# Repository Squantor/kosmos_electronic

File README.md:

# Kosmos electronic bits and pieces
This repository contains various bits and pieces that can be used with the Kosmos electronic series experiment kits. 
## Structure
* [Electronics](electronics/README.md) contains the schematics and PCB's used by the project

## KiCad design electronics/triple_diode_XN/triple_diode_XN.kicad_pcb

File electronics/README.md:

# Kosmos electronic modules
This directory contains mostly reproductions or new modules for the Kosmos electronics experiment kits. The schematics and PCB's are drawn in kicad. Most of the modules are described in "unit cells". The transistor modules are one unit cell large. The MW/AM module and opamp module are two unit cells large. The 555 module from the XN3000 box is a 3 cell large module.

There exist also "double density" modules used in the XN3000 series box. Here the unitcell is subdivided, this to acommodate components with high pin counts like the LM324 quad opamp or some 4000 series logic. I might need to modify some XN boards to measure the size of these modules so I might prototype them.

The [Kosmos electronic radio tech](https://www.youtube.com/watch?v=OwKrZVnxMPc) has a few very interesting modules. I would love to get my hands on those and try some experiments with them and recreate the modules. It contains 

But why not create your own modules? I have a few ideas, useful for all kinds of experiments and prototyping. Feel free to add an issue for module ideas to add them to the planned modules.
# Created modules
* [one by one cell template](template_1by1/README.md)
* [one by two cell template](template_1by2/README.md)
* [one by three cell template](template_1by3/README.md)
* [two by two cell template](template_2by2/README.md)
* [one by one cell prototyping board](proto_1by1/README.md)
* [one by two cell prototyping board](proto_1by2/README.md)
* [two by two cell prototyping board](proto_2by2/README.md)
* [NPN transistor Through Hole](NPN_transistor_TH/README.md)
* [PNP transistor Through Hole](PNP_transistor_TH/README.md)
* [NMOS transistor Through Hole](NMOS_transistor_TH/README.md)
* [PMOS transistor Through Hole](PMOS_transistor_TH/README.md)
* [Generic transistor SOT23](transistor_SOT23/README.md)
# Planned modules
* Prototyping boards for all the templates, useful for adding your own circuits
* TL431 adjustable zener
* NE555 just like in the XN3000 box
* General purpose dual opamp board, fit with a socket so any dual opamp can be fitted
* LM321 single opamp
* Audio Amp module as used in the X2000 and XN2000 based on the [TBA820M](https://lcsc.com/product-detail/Audio-Power-OpAmps_UTC-Unisonic-Tech-TBA820ML-D08-T_C171467.html)
* Single optocoupler
* Dual photodiode optocoupler, useful for analog isolator experiments?
* SA612 gilbert cell mixer, this module was used in the Kosmos electronic radio tech but has an unusual size, seems like a 2 by 2 unit cell module but fitting a higher density top?
* SA612 gilbert cell mixer but in a three by one format, more useful for all kinds of experiments
* Crystal/filter on a single cell module, the filter was present in the radio tech box
* SA612 mixer based down converter, to make a X1000/XN1000 short wave radio or a direct conversion receiver.
# TODO's

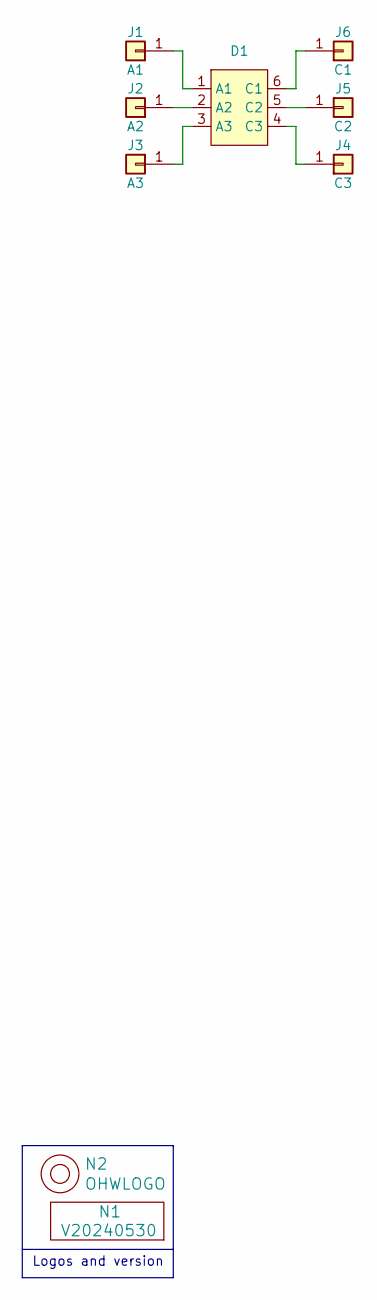
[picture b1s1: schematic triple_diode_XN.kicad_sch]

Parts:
D1: SOT363-NXP-hand
J1: A1; PC_pin_nail_head_6092
J2: A2; PC_pin_nail_head_6092
J3: A3; PC_pin_nail_head_6092
J4: C3; PC_pin_nail_head_6092
J5: C2; PC_pin_nail_head_6092
J6: C1; PC_pin_nail_head_6092
N1: V20240530; Label_Generic
N2: OHWLOGO; OSHW-Symbol_6.7x6mm_SilkScreen

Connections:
unnamed: D1.1 (A1), J1.1
unnamed: D1.2 (A2), J2.1
unnamed: D1.3 (A3), J3.1
unnamed: D1.6 (C1), J6.1
unnamed: D1.5 (C2), J5.1
unnamed: D1.4 (C3), J4.1

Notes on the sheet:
Logos and version

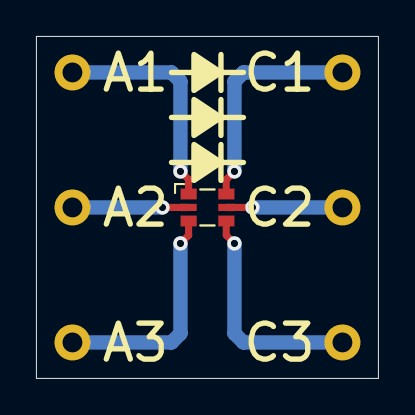
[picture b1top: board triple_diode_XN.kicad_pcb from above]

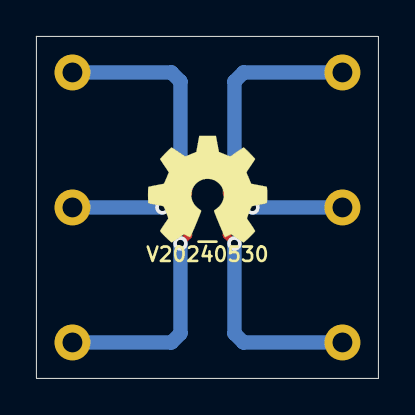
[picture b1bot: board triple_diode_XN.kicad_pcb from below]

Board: 2 copper layers, 19.0 x 19.0 mm, 9 parts (2 on the bottom side), 6 nets.

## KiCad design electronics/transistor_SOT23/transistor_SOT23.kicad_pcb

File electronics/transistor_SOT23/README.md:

# Kosmos electronic SOT23 transistor
Kosmos electronic generic SOT23 transistor, as far as I know most SOT23 transistors, BJT or MOSFET, all have the same pinout.
1. Base or Gate
2. Emitter or Source
3. Collector or Drain
## TODO's
Still some things need to be done:
* Manufacturing
* Test
* Pictures
## BOM
* Kosmos electronic uses some special pins for the connections, I have found something similar by [Mill-max 6092](https://www.mill-max.com/catalog/download/2020-10%3A207M.pdf) available at [digikey](https://www.digikey.com/en/products/detail/mill-max-manufacturing-corp/6092-0-00-15-00-00-33-0/1991698)
* BC547 style PNP transistor

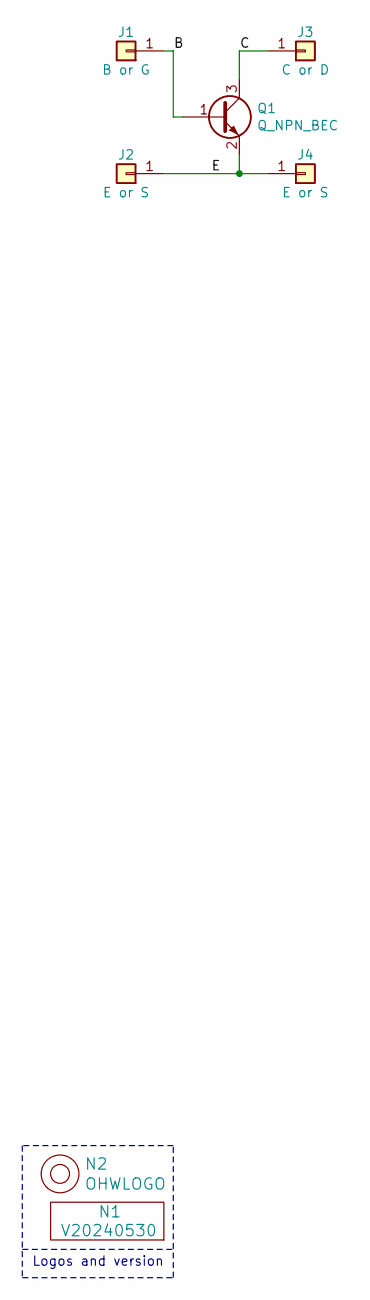
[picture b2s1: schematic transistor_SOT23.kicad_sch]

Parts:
J1: B or G; PC_pin_nail_head_6092
J2, J4: E or S; PC_pin_nail_head_6092
J3: C or D; PC_pin_nail_head_6092
N1: V20240530; Label_Generic
N2: OHWLOGO; OSHW-Symbol_6.7x6mm_SilkScreen
Q1: Q_NPN_BEC; SOT23-3

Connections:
/B: J1.1, Q1.1 (B)
/C: J3.1, Q1.3 (C)
/E: J2.1, J4.1, Q1.2 (E)

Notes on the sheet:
Logos and version

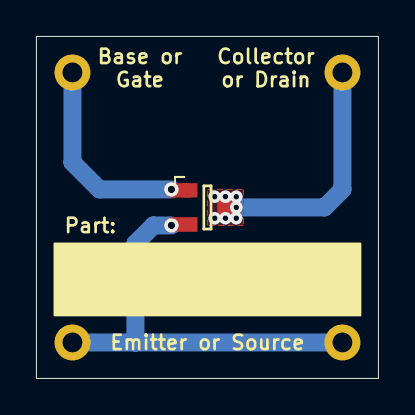
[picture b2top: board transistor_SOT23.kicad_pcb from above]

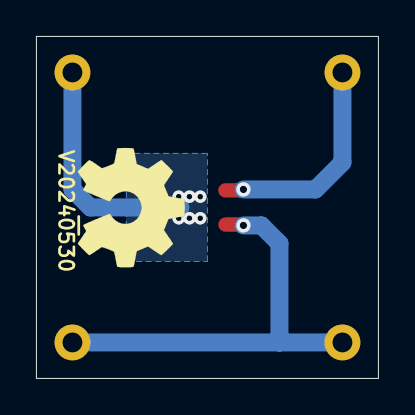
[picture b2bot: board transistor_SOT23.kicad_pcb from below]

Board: 2 copper layers, 19.0 x 19.0 mm, 7 parts (2 on the bottom side), 3 nets.

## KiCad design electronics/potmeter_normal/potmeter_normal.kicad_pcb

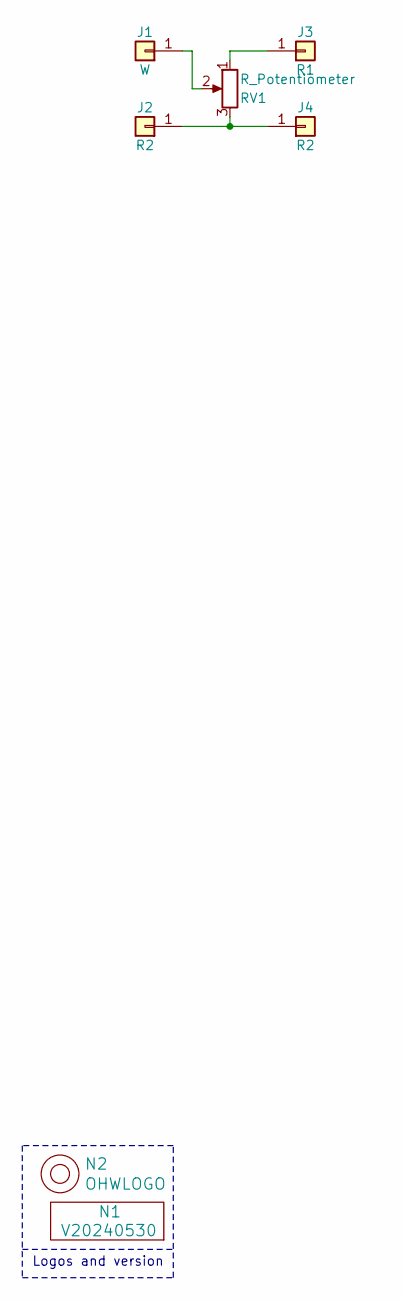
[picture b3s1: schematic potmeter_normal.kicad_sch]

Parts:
J1: W; PC_pin_nail_head_6092
J2, J4: R2; PC_pin_nail_head_6092
J3: R1; PC_pin_nail_head_6092
N1: V20240530; Label_Generic
N2: OHWLOGO; OSHW-Symbol_6.7x6mm_SilkScreen
RV1: R_Potentiometer; Potentiometer_Piher_PT-15-V15_Vertical

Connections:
unnamed: J1.1, RV1.2
unnamed: J2.1, J4.1, RV1.3
unnamed: J3.1, RV1.1

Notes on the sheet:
Logos and version

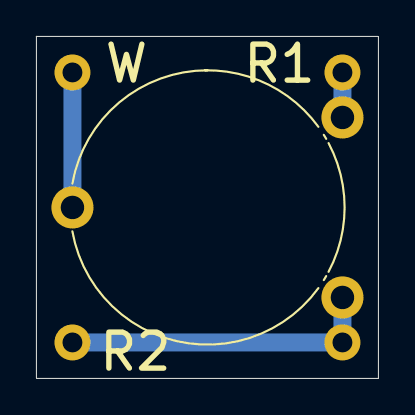
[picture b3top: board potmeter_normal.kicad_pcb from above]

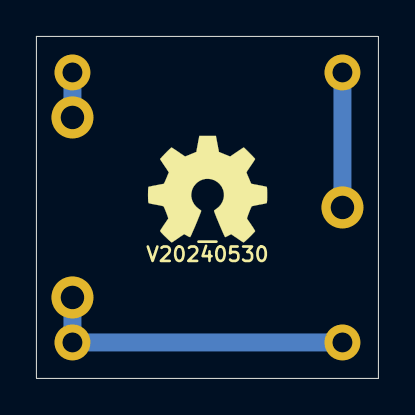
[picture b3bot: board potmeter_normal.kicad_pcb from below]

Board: 2 copper layers, 19.0 x 19.0 mm, 7 parts (2 on the bottom side), 3 nets.

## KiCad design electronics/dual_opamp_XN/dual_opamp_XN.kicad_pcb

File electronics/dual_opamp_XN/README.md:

# One by Two module template high density for Kosmos Elektronic XN
Template for a one by two sized module for the Kosmos XN1000 series experiment boxes.
## BOM
* The X1000 and XN1000 special pins for the connections, I have found something similar by [Mill-max 6092](https://www.mill-max.com/catalog/download/2020-10%3A207M.pdf) available at [digikey](https://www.digikey.com/en/products/detail/mill-max-manufacturing-corp/6092-0-00-15-00-00-33-0/1991698)

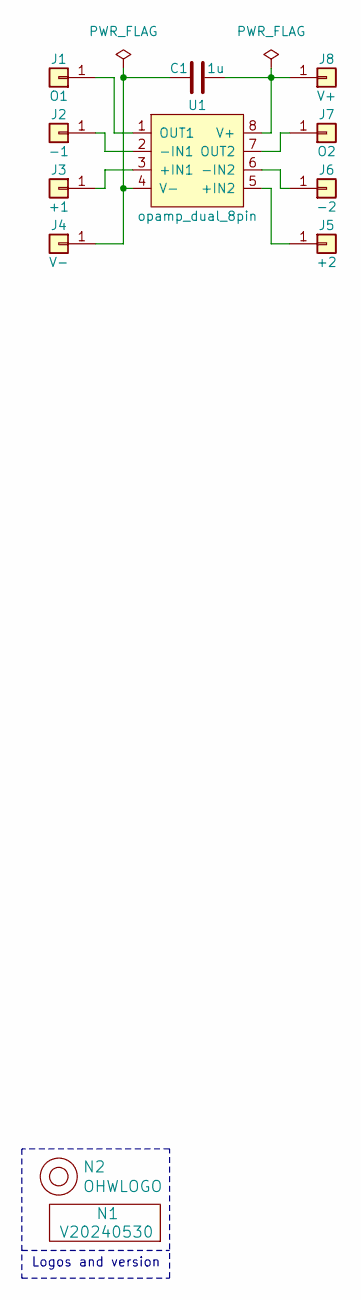
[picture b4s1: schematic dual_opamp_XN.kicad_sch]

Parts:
C1: 1u; C-050-050X100-0805-3516-film
J1: O1; PC_pin_nail_head_6092
J2: -1; PC_pin_nail_head_6092
J3: +1; PC_pin_nail_head_6092
J4: V-; PC_pin_nail_head_6092
J5: +2; PC_pin_nail_head_6092
J6: -2; PC_pin_nail_head_6092
J7: O2; PC_pin_nail_head_6092
J8: V+; PC_pin_nail_head_6092
N1: V20240530; Label_Generic
N2: OHWLOGO; OSHW-Symbol_6.7x6mm_SilkScreen
U1: opamp_dual_8pin; DIP-8_W7.62mm_Socket

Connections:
unnamed: J1.1, U1.1 (OUT1)
unnamed: J2.1, U1.2 (-IN1)
unnamed: J3.1, U1.3 (+IN1)
unnamed: C1.1, J4.1, U1.4 (V-)
unnamed: J5.1, U1.5 (+IN2)
unnamed: J6.1, U1.6 (-IN2)
unnamed: J7.1, U1.7 (OUT2)
unnamed: C1.2, J8.1, U1.8 (V+)

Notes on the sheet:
Logos and version

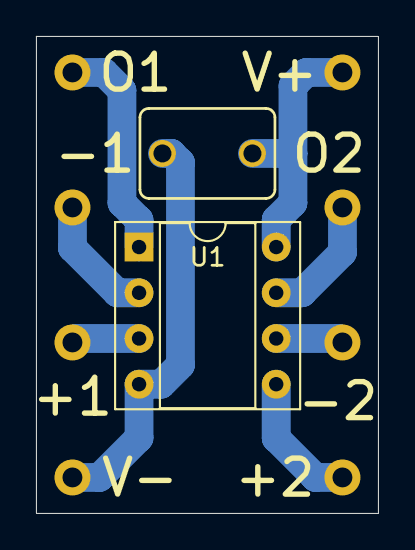
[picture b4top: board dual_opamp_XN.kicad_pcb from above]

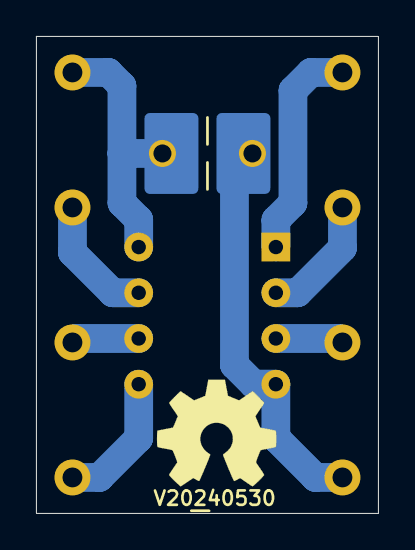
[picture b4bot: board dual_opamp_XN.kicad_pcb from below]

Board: 2 copper layers, 19.0 x 26.5 mm, 12 parts (2 on the bottom side), 8 nets.

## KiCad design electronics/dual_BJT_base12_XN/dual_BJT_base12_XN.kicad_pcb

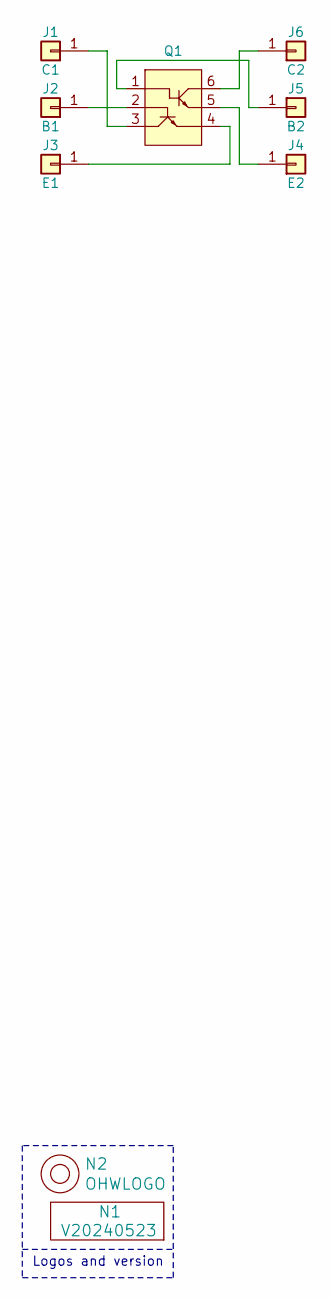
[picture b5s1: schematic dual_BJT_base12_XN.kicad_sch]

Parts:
J1: C1; PC_pin_nail_head_6092
J2: B1; PC_pin_nail_head_6092
J3: E1; PC_pin_nail_head_6092
J4: E2; PC_pin_nail_head_6092
J5: B2; PC_pin_nail_head_6092
J6: C2; PC_pin_nail_head_6092
N1: V20240523; Label_Generic
N2: OHWLOGO; OSHW-Symbol_6.7x6mm_SilkScreen
Q1: SOT363-NXP-hand

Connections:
unnamed: J1.1, Q1.3
unnamed: J2.1, Q1.2
unnamed: J3.1, Q1.4
unnamed: J4.1, Q1.5
unnamed: J5.1, Q1.1
unnamed: J6.1, Q1.6

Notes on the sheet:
Logos and version

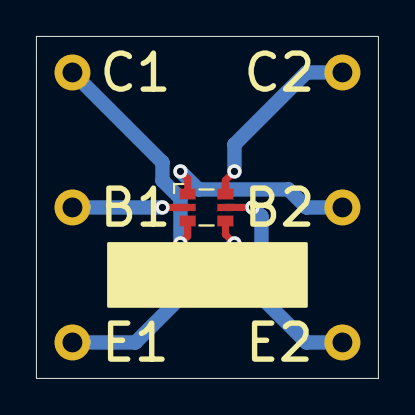
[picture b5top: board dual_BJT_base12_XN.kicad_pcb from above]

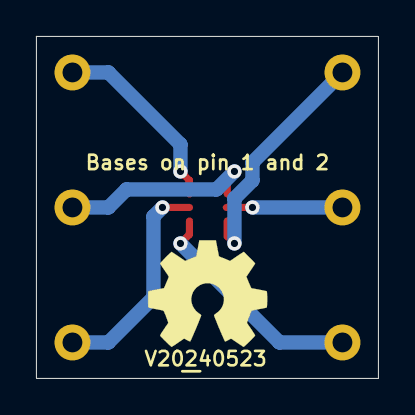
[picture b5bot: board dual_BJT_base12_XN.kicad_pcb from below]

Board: 2 copper layers, 19.0 x 19.0 mm, 9 parts (2 on the bottom side), 6 nets.

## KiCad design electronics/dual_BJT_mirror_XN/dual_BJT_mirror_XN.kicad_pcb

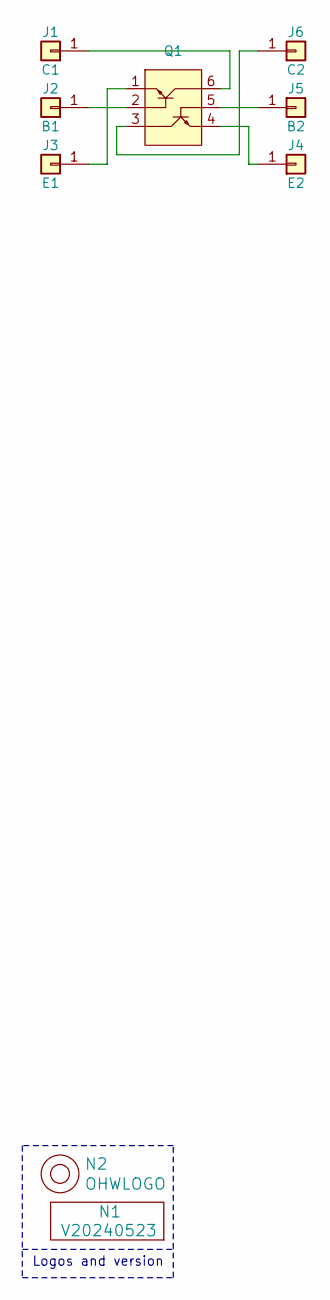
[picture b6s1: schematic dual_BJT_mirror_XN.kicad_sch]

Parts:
J1: C1; PC_pin_nail_head_6092
J2: B1; PC_pin_nail_head_6092
J3: E1; PC_pin_nail_head_6092
J4: E2; PC_pin_nail_head_6092
J5: B2; PC_pin_nail_head_6092
J6: C2; PC_pin_nail_head_6092
N1: V20240523; Label_Generic
N2: OHWLOGO; OSHW-Symbol_6.7x6mm_SilkScreen
Q1: SOT363-NXP-hand

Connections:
unnamed: J1.1, Q1.6
unnamed: J2.1, Q1.2
unnamed: J3.1, Q1.1
unnamed: J4.1, Q1.4
unnamed: J5.1, Q1.5
unnamed: J6.1, Q1.3

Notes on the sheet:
Logos and version

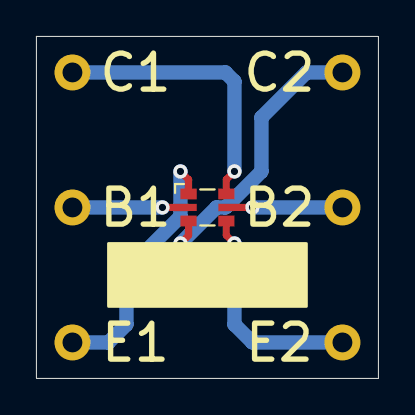
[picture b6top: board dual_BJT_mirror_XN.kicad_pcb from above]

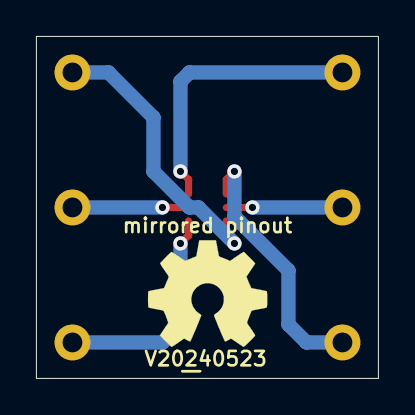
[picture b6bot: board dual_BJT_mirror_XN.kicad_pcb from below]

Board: 2 copper layers, 19.0 x 19.0 mm, 9 parts (2 on the bottom side), 6 nets.

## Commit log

2020-11-18 added some documentation
2020-11-18 added one unit cell template, added gitignore, added PCB library submodule
2020-11-18 added mill max library
2020-11-18 initial creation of template schematic, updated versionnumber
2020-11-18 fixed incorrect footprint name for one pin
2020-11-18 finished one unit cell
2020-11-18 updated readme for the one unit template
2020-11-18 added NPN transistor module
2020-11-18 initial placement
2020-11-18 adapted some silk line thicknesses
2020-11-18 copied NPN tot PNP transistor
2020-11-18 forgot rename action
2020-11-18 changed NPN to PNP transistor
2020-11-18 final changes to PNP transistor
2020-11-18 updated documentation
2020-11-19 initial add of two unit kosmos module template
2020-11-19 template two units for kosmos modules
2020-11-19 initial template copy for three cell kosmos module
2020-11-19 updated schematic with additional pins
2020-11-19 added template for a three unit kosmos module
2020-11-19 updated documentation, added planned and module ideas
2020-11-20 big rename action
2020-11-20 updated documentation on the templates
2020-11-20 updated documentation, added few extra ideas, added 2 by 2 cell template
2020-11-20 finished 2 by 2 unit template
2020-11-20 updated 1 by 1 template
2020-11-20 locked pins and updated versionnumber
2020-11-20 fixed documentation error
2020-11-20 initial copy of the template to prototying board
2020-11-20 added prototyping area to 1 by 1 module
2020-11-21 added first kosmos grid
2020-11-21 placed and routed
2020-11-21 removed labels and open hardware logo
2020-11-21 applied removed labels
2020-11-21 added 1 by 2 prototyping grid
2020-11-21 updated PCB library due to kosmos proto grids
2020-11-22 renamed files
2020-11-22 initial creation of 2 by 2 proto board
2020-11-22 updated newer kosgrid footprints
2020-11-22 changed protogrid, updated versionnumber
2020-11-22 updated PCB library
2020-11-22 updated versionnumber
2020-11-22 removed defunct labels
2020-11-22 placed and routed 2 by 2 grid
2020-11-22 forgotten some labels to remove from silk
2020-11-22 updated documentation to include the prototyping boards
2020-11-22 copied over NPN to NMOS transistor module
2020-11-22 added NMOS transistor, BS170 style
2020-11-22 added annotation
2020-11-22 changed to bit wider footprint
2020-11-22 routed and completed NMOS silk artwork
2020-11-22 forgot to rename, now done
2020-11-22 added PMOS transistor, copied from NMOS transistor
2020-11-22 changed to PMOS transistor
2020-11-22 completed PMOS module
2020-11-22 fixed NMOS transistor module
2020-11-22 small modifications on NPN module
2020-11-22 small fixes to PNP transistor module
2020-11-22 small fixes
2020-11-22 fixed incorrect versionnumbers
2020-11-22 added generic SOT-23 module
2020-11-22 updated documentation reference to generic SOT23 module
2020-11-22 removed superfluous labels/silk, added writable label
2020-11-23 small pcb update
2020-11-23 updated versionnumber location
2020-11-23 started with AMP module clone
2020-11-23 added more cap footprints
2020-11-25 updated capacitor footprints, given boucherot filter R a value, updated versionnumber
2020-11-25 updated footprints and values, but also ripped up all traces, they need to be on the bottom
2020-11-25 updated capacitor library
2020-11-25 updated footprints
2020-11-25 routed all traces, placed silk and connections
2020-11-26 started with the single opamp module
2020-11-26 schematic and board completed
2020-11-26 completed silkscreen art
2020-11-27 fixed ERC errors
2020-11-27 fixed DRC errors and updated versionnumber
2020-11-27 small schematic fixxes, updated versionnumber
2020-11-27 updated versionnumber, small schematic fixes
2020-11-27 prettified version location
2022-01-08 added board link
2022-01-08 ignore freecad backup files
2022-01-13 updated submodules
2022-01-13 added 555 timer module from XN3000
2022-01-13 changed font size on the templates
2022-01-13 added inital operator desk 3dmodel
2024-05-03 updated kicad 7 ignores
2024-05-03 added XN high density templates
2024-05-06 added Kosmos high density X templates and completed high density XN templates
2024-05-06 completed high density X templates, updated versionnumbers of high density XN templates
2024-05-22 added universal NPN transistor PCB
2024-05-22 added universal NPN transistor board
2024-05-22 added universal PNP transistor board
2024-05-23 added TL431 board
2024-05-23 converted template 1by3 to kicad 7
2024-05-23 added normal dual opamp board
2024-05-23 added dual opamp XN high density variant
2024-05-23 changed name to reflect project name
2024-05-23 converted to kicad 7
2024-05-23 started with dual NBJT with a mirror footprint
2024-05-23 SOT363 dual NBJT mirror transistor
2024-05-24 renamed XN dual opamp
2024-05-24 renamed BJT
2024-05-25 added another XN board
2024-05-25 rename
2024-05-25 added dual BJT transistor with SOT363 and the bases on pin 1 and 2
2024-05-25 updated symbol/footprint tables
2024-05-25 accidentaly deleted files
2024-05-25 added dual BJT with base on pin 1,2 for XN
2024-05-25 added transistor library
2024-05-25 added normal density SOT363 breakout
2024-05-25 fixes and added SOT363 breakout for XN density
2024-05-25 small changes
2024-05-25 added breakouts for SOT23-6 normal and XN high density
2024-05-26 added piher trimpot module
2024-05-26 potmeter rename
2024-05-26 updated to newer version
2024-05-26 added SOT23 breakout
2024-05-26 added triple diodes
2024-05-30 renames
2024-05-30 review changes
2024-05-30 added panel
2024-05-30 panelized
2024-05-30 review updates
2024-05-30 small updates and created a panel
2024-05-30 review updates and tiled variant
2024-05-30 updates and tiled
2024-05-30 review updates, added tiled version
2024-05-30 reduced tiled sizes and some minor changes
